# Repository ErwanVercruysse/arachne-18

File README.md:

<div align="center">

# ARACHNE / 18 — v4

**Six legs. Eighteen servos. Three monolithic moving links per leg.**

**18 × STS3215 12 V** · **3D printable** · **Onshape** · **MuJoCo + BAM**

[Onshape assembly](https://cad.onshape.com/documents/88edbeda4232642329938c14/w/19f5435855c2974f02fa7c68/e/916e6d95108202647e946643) · [Download print pack](print/ARACHNE_18_v4_print_pack.zip) · [Build guide](docs/build-guide.md) · [Simulation setup](docs/another-computer.md)

</div>

> **Deze fork (KVR-CIBER):** het ontwerp, de CAD en de simulatie hieronder zijn van [Tom Michiels](https://github.com/Tom-Michiels/arachne-18). Kobe heeft de robot echt gebouwd en er deze software voor geschreven, samen met [Claude Code](https://claude.com/claude-code).
>
> | Wat | Waar |
> |---|---|
> | Alle 18 servo's gekalibreerd, gewrichtslimieten gemeten | [`calibration/`](calibration/) |
> | Bewegingen op de echte robot: opstaan, lopen, draaien, dansen | [`tools/stand.py`](tools/stand.py), [`walk.py`](tools/walk.py), [`spin.py`](tools/spin.py), [`dance.py`](tools/dance.py), [`motion.py`](tools/motion.py) |
> | Besturen met een Bluetooth-gamepad, veilig via geplande gangen | [`tools/gamepad_robot.py`](tools/gamepad_robot.py), [`plan_gaits.py`](tools/plan_gaits.py) |
> | Live 3D-tweeling + camera + cockpit in de browser, met login | [`tools/live_twin.py`](tools/live_twin.py), [`tools/web/`](tools/web/), [`auth.py`](tools/auth.py) |
> | MuJoCo-simulatie in de browser | [`tools/sim_world.py`](tools/sim_world.py), [`tools/web/sim.html`](tools/web/sim.html) |
> | v4-robot van Tom Michiels samengevoegd (eendelige poten, 62 mm coxa, TPU-schoen): simulatie en beleid gebruiken de v4-maten | [`docs/revision-v4.md`](docs/revision-v4.md) |
> | Zelf lopen: het getrainde beleid live op de robot, met de IMU; houdt zich vlak op hellingen, tilt de poten hoger op oneffen grond | [`tools/policy_walk.py`](tools/policy_walk.py), [`terrain_gait.py`](tools/terrain_gait.py), [uitleg](docs/self-walking.md) |
> | Valbeveiliging: vrije val of omkantelen → zacht landen | [`tools/fall_guard.py`](tools/fall_guard.py), [`training/fall_test.py`](training/fall_test.py) |
> | Pakken: op vier poten iets van 12-15 cm breed oppakken met de voorpoten | [`tools/grab.py`](tools/grab.py), [`training/grab_test.py`](training/grab_test.py) |
> | BAM-metingen (38 / 173 / 263 / 383 g) en identificatie | [`bam_data/`](bam_data/), [`simulation/bam_identify.py`](simulation/bam_identify.py) |
> | ESP32-C3 one-wire firmware voor de STS3215-bus | [`firmware/`](firmware/) |
> | Android-app (wifi-scan, cockpit, "hey spin") | [arachne-app](https://github.com/KVR-CIBER/arachne-app) |

ARACHNE 18 is a compact six-legged prototype built around the owner's eighteen Feetech STS3215 12 V servos. This revision integrates the v4 leg and chassis into the complete robot: a single printed chassis, six identical leg modules, a removable controller carrier, and an organic ventilated canopy.

Each moving link is one printed piece. The tibia is symmetric, the horn cheeks have equal spacing, and the case cradles use the servo's factory mounting points. Local openings on the dummy side provide connector access. Horns sit inside the forks; recessed DIN 7380 button-head screws sit outside. There are no loose structural shims.

| Specification | v4 |
|---|---|
| Mechanism | Six yaw–hip–knee chains; 18 revolute joints |
| Chassis | 194 × 173.5 × 56 mm; six mounts on an 86 mm radius |
| Link geometry | Coxa 62 mm; hip offset −6.95 mm; femur 78 mm |
| Measured horn span | 36.5 mm; driven horn 2.5 mm, dummy horn 2.0 mm |
| Forks | 36.9 mm internal span; 5.5 mm cheeks; Ø7.3 mm center access |
| Battery envelope | 115 × 40 × 35 mm, excluding protruding plugs |
| Controller envelope | 90 × 60 × 18 mm; configurable 64 × 48 mm hole pattern |
| Printed parts | 8 unique files; 31 pieces including 6 TPU shoes and 4 PCB standoffs |
| Modelled hardware | 160 DIN 7380 M3 screws, 72 supplied PA2 case screws, 16 M3 inserts, 36 horns |
| Simulation | 19 rigid links, 18 actuators, 336 visual parts; estimated mass 2.333 kg |

## Inside the robot

| Removable electronics carrier | Symmetric six-leg layout |
|---|---|
|  |  |

The battery rests on the chassis and is retained by two straps. Four integrated posts support the controller carrier. Its mounting screws are reached through deep open wells. Two recessed M3 screws hold the canopy; straight tool openings make them accessible from above. Four small standoffs provide a 6 mm PCB air gap.

The front and rear pairs can touch their toes through a checked coordinated pose: inward yaw approximately 57.51°, hip −20°, knee 0°. This is a reach pose, not a walking command. Independent joint limits do not guarantee arbitrary combinations are collision-free.

## Print and assemble

Download the [STL bundle](print/ARACHNE_18_v4_print_pack.zip), [assembled STEP](cad/ARACHNE_18_assembly.step), or [individual STEP parts](cad/parts). STL units are millimetres; use 100% scale and the supplied orientations. All parts fit the H2D.

Start with one complete leg and a real servo. The [build guide](docs/build-guide.md) explains mounting order, screw lengths, insert positions, connector clearance and support removal. M3 plastic-thread joints use **Ruthex RX-M3x5.7**, with **Ø4.0 × 7 mm pilots**. Horn screws thread into metal horns; supplied case screws thread into the servo's factory mounting points.

The structural pieces have continuous flat bed faces. The curved canopy needs internal support; support is also needed locally beneath some fork bridges. All eight parts were sliced successfully with an A1 geometry proxy profile. **Reslice for your H2D**; no machine-ready G-code is supplied.

## Run MuJoCo

From a fresh clone, with Python 3.12:

```sh
git clone https://github.com/Tom-Michiels/arachne-18.git
cd arachne-18
python3.12 -m venv .venv
source .venv/bin/activate
python -m pip install -r simulation/requirements.txt
python simulation/simulate.py --headless --seconds 10 --voltage 11.1
python simulation/validate.py
```

For an interactive viewer on macOS:

```sh
mjpython simulation/grounded_demo.py --seconds 300
```

Use `python` for the viewer on Linux/Windows. On Windows activate with `.venv\Scripts\activate`. See [setup on another computer](docs/another-computer.md) and the [simulation guide](docs/simulation.md).

The animation is a BAM-driven body-height exercise. All six feet remain in contact; the base is free. The 12 V actuator parameters are an explicitly labelled approximation derived from BAM's identified 7.4 V model and manufacturer operating points. [BAM assumptions](docs/bam-model.md).

## Existing RL work

**No RL retraining was performed for v4.** Existing checkpoints, measurements and walking/jump/terrain videos are preserved. They were produced with earlier geometry and do not establish v4 performance. The training model and inverse kinematics now use v4 dimensions; controller and geometry compatibility tests are included.

### Browser simulation and cockpit (this fork)

`tools/live_twin.py` also serves a physics simulation at `/sim` (on the robot: `http://spin.local:5870/sim`). Everyone on the network sees and drives the same virtual robot: pick which parts to show (hidden parts also leave the physics mass), drive with the pad or WASD/QE in tripod, ripple or wave gait, tilt the body, run the shows, or run the real robot scripts (`stand.py`, `walk.py`, `spin.py`, `dance.py`) unchanged against virtual STS3215 servos. The meter panel shows supply current and voltage sag (5 A lab supply, 10 A, 3S LiPo, with brown-out), torque per servo, foot forces and the stability margin. The real servos are never touched.

```sh
.venv/bin/python tools/live_twin.py          # http://localhost:5870/sim
tools/deploy_pi.sh                           # copy to the Pi and restart the arachne-twin service
```

`/cockpit` puts the camera feed, the 3D view and the controls on one screen for a landscape tablet. It shows a picture-in-picture that you tap to swap. It has touch sticks, every move as a button, and gamepad support (Xbox/Recon or PlayStation, over USB or Bluetooth).

Cameras are found automatically:
- the Pi camera (`rpicam-vid`);
- USB webcams (`/dev/v4l/by-id/*usb*`, via ffmpeg);
- any MJPEG command in `ARACHNE_CAMERA`, `ARACHNE_CAMERA_1`, and so on.

Streams are served at `/camera.mjpg?cam=N`. A Pi 4 has a single CSI connector, so a second camera has to be USB.

An MPU6050 on I2C (SDA GPIO2, SCL GPIO3) is read by `tools/imu.py`. It appears in `/state` and in the cockpit. Its axes still have to be matched to the body by tilting the robot by hand.

The Android app (`~/arachne-app`, Capacitor) works like this:
- It scans the wifi for the twin.
- It opens the cockpit with an on-device voice assistant: say "hey spin, dans", "kom naar mij", "draai om" or "hoeveel volt?".
- Without a key it understands fixed Dutch commands. With a Claude API key it answers free questions and chooses moves through tool calls.
- Turning and walking distances are closed-loop on the measured pose.

[Training documentation](training/README.md) · [Archived locomotion videos](https://tom-michiels.github.io/arachne-18/) · [Revision notes](docs/revision-v4.md)

## Validation and limitations

Eight valid single-solid print parts and eight watertight single-component STLs pass the current checks. The release includes screw/print clearance checks, driver access checks, the isolated leg's factory-hole and connector tests, chassis installation tests, sampled dorsal motion and paired-toe reach evidence. MuJoCo passes topology, joint axes, standing at three voltages, reset reproducibility and grounded motion checks. [Scope and reports](docs/validation.md).

This is a digitally checked prototype. Real servo/horn/plug fit, print tolerances, insert pull-out strength, fatigue and payload capacity need a physical one-leg trial. The controller and battery are envelopes because exact models have not been specified. Servo visuals are simplified exterior references; the original vendor STEP is retained for mechanical checks.

## Files and sources

| Folder | Contents |
|---|---|
| [cad](cad) | Assembly, unique-part layout, individual STEP solids, dimensions and reference geometry |
| [print](print) | Oriented STLs, print quantities and downloadable print pack |
| [simulation](simulation) | MJCF, local-frame meshes, BAM parameters, runtime and validation |
| [src](src) | Parametric CadQuery source, exporters, CAD checks and Onshape mate tooling |
| [docs](docs) | English build, simulation, validation and development guides |
| [training](training) | Updated model adapter and preserved historical RL work |
| [tools](tools) | Real-robot tools: servo driver, calibration, live twin + browser simulation (`/sim`), motion scripts, Pi deploy |

Actuator modelling uses [Rhoban/BAM](https://github.com/Rhoban/bam); simulation uses [MuJoCo](https://github.com/google-deepmind/mujoco). See [third-party notices](THIRD_PARTY_NOTICES.md). No project-wide open-source license has been selected; bundled BAM material retains its Apache-2.0 license.

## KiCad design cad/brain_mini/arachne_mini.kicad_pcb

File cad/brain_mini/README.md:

# ARACHNE-18 mini brain board (v1.0)

Small 4-layer servo/IMU board for the hexapod that works **with the existing Raspberry Pi 4**: no CM5, no PI LINK.
The Pi talks to the ESP32-S3 over **one USB-C (board) <-> USB-A (Pi) cable** and gets its 5 V from the board.
It is the big board (`cad/brain_pcb`) without the CM5 part: same buck, 12 V entry, servo buses and IMU circuits.

| Block | Part | What it does |
|---|---|---|
| Real-time | **ESP32-S3-WROOM-1-N16R8** | drives both servo buses, reads the IMU, native USB to the Pi (`/dev/ttyACM0`) |
| IMU | **MPU-6050** (I2C on the ESP32, INT on IO6) | near the middle of the board |
| Sensors | G-V-S strip + 2x Qwiic | 19 free GPIOs, each with GND + 3.3 V, plus I2C |
| Servo buses | 2x (74AHCT1G126 + 74LVC1G34) | Feetech STS half-duplex, 5 V levels, 1 Mbaud |
| Legs | 6x Molex Mini-SPOX 5267-03A (22-03-5035, 2.50 mm, chamfered) | bus A = L1 L2 L3 (right), bus B = L4 L5 L6 (left) |
| Power | 2 big solder pads, P-MOSFET reverse protection, TVS, 2x 330 uF | 12 V straight to the servos |
| 5 V | TI **TPS54560B** buck, 5 V 5 A | Pi 4 (via the **5V PI** pads) + ESP32 + bus drivers |

Board: **92 x 70 mm**, 1.6 mm, 4 layers (F signals / In1 GND / In2 12 V / B signals + 5 V band to the Pi pads),
R6 corners, 4x M3 (3.2 mm) at (±41.5, ±25.5). Mounts on acrylic plate **v4**
(`cad/electronics_plate/make_electronics_plate_v4.py`): M3 x 12 -> PCB -> 8 mm spacer -> plate -> nut.

## Connections

* **USB-C "USB > PI 4"**: USB-C to USB-A cable to any Pi 4 USB port. Flash the ESP32 from the Pi
  (`arduino-cli` / `esptool` over `/dev/ttyACM0`) or from the Mac with the same cable. The Pi's 5 V on this cable
  only feeds the ESP32 side (through SS14 D7), so the ESP32 can be flashed without the 12 V battery.
* **5V PI pads** (top edge, next to the buck): 5 V / 3 A out for the Pi 4. Solder an 18-20 AWG pair to the Pi's
  GPIO pin 2 or 4 (+5 V) and pin 6 (GND), or to a cut USB-C lead plugged into the Pi power socket.
* **12V IN pads** (bottom-left): battery, 14-16 AWG; zip-tie slots on plate v4 as strain relief.
* **Servo (each leg):** `1 = GND, 2 = +12 V, 3 = DATA` (silkscreen G V S). Check against your cable first!

## ESP32-S3 pins

| GPIO | function | GPIO | function |
|---|---|---|---|
| 17 / 18 / 16 | bus A TX / RX / DE (UART1, DE = RTS) | 4 / 5 / 6 | IMU SDA / SCL / INT |
| 10 / 11 / 9 | bus B TX / RX / DE (UART2) | 1 | 12 V sense (100k/15k: V = adc x 7.67) |
| 19 / 20 | USB D- / D+ (to the Pi) | 2 | blue LED |
| 0 / EN | BOOT / RESET buttons | | |

**Sensor strip (bottom edge):** every free GPIO has its own **G - V - S** column (2.54 mm), like an Arduino sensor
shield, so a standard 3-wire sensor cable (GND, VCC, signal) plugs straight on.
* **V = 3.3 V.** The ESP32 pins are NOT 5 V tolerant: use 3.3 V sensors, or a level shifter for 5 V ones.
* Columns from left to right: IO7, IO15, IO8, IO3\*, IO46\*, IO12, IO13, IO14, IO21, IO47, IO48, IO45\*, IO38, IO39,
  IO40, IO41, IO42, TX43, RX44. The name is printed above every column.
* Next to the strip: **2x Qwiic / STEMMA QT** (JST-SH 4-pin, 3.3 V I2C, the same bus as the MPU-6050 on IO4/IO5).

\* strapping pins: don't pull them up/down at boot. IO35-37 are used by the octal PSRAM (N16R8).

**Servo connectors:** Molex Mini-SPOX **5267-03A** vertical headers (22-03-5035), the mating header for the **5264** plugs
(2.5 mm, with the chamfered corners) on the Feetech STS3215 / Waveshare cables. The chamfered side of the silkscreen
shows which way the plug goes in.

## Files

| File | |
|---|---|
| `arachne_mini.kicad_pro / .kicad_sch / .kicad_pcb` | open in KiCad 10 |
| `fab/` | gerbers zip, BOM + CPL with LCSC numbers for JLCPCB, schematic PDF, renders |
| `tools/design.py` | **single source of truth**: every part, net and position |
| `tools/build_all.sh` | regenerates everything (libraries, schematic, board, Freerouting + A* finisher, checks, fab) |

## Order (JLCPCB)

4 layers, 1.6 mm, upload `fab/arachne_mini_gerbers_JLCPCB.zip`, then BOM + CPL for assembly (LCSC numbers filled in).
The ESP32 antenna overhangs the top edge by ~6 mm on purpose.

## Before the first power-up

1. 12 V on the pads without Pi or servos: green LED, measure 5.0 V on the 5V PI pads and 3.3 V.
2. Connect the Pi (5V PI pads + USB cable), flash the ESP32.
3. Servos one leg at a time (torque on one servo at a time, 30 %).

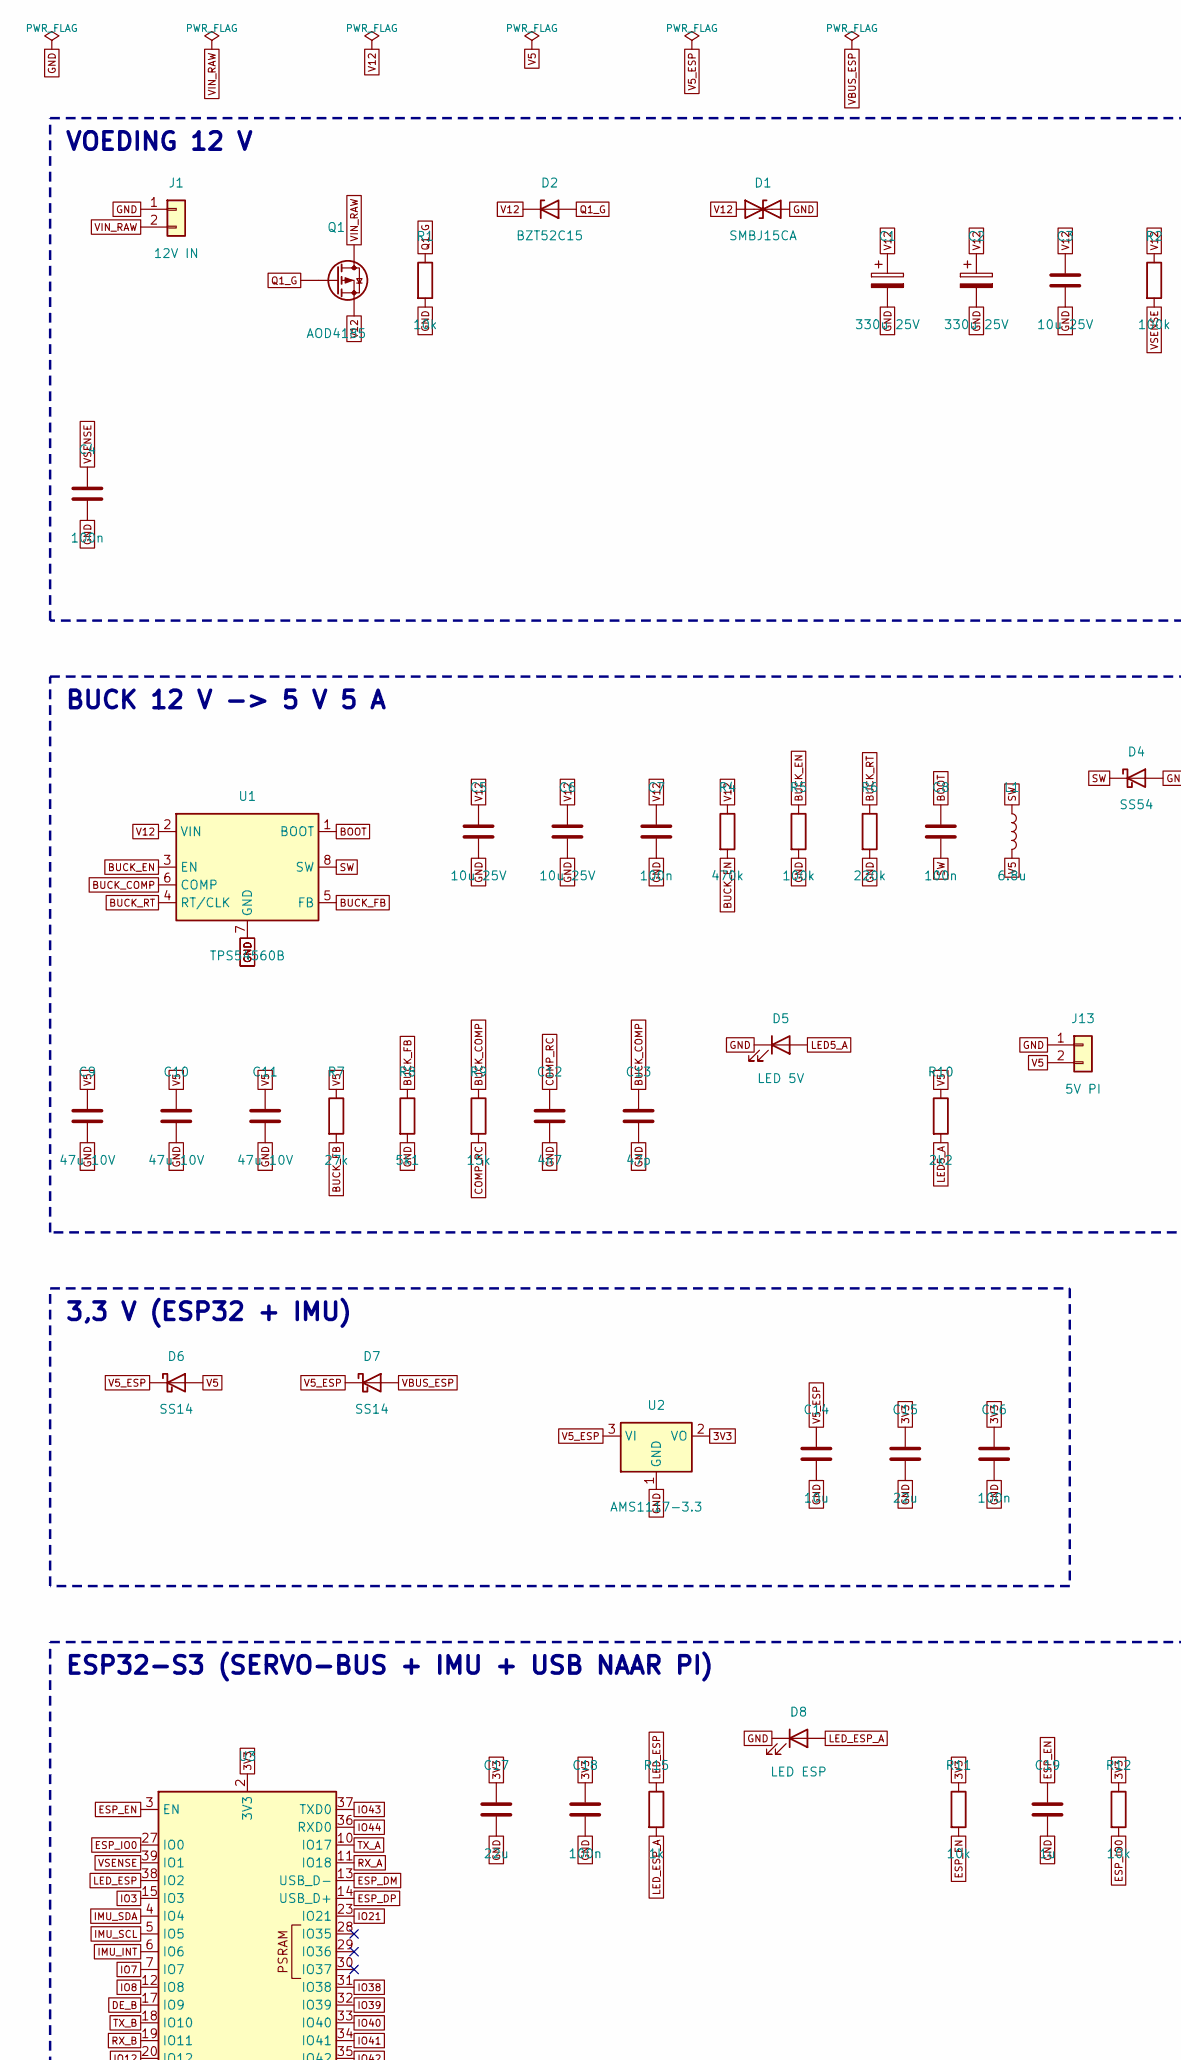
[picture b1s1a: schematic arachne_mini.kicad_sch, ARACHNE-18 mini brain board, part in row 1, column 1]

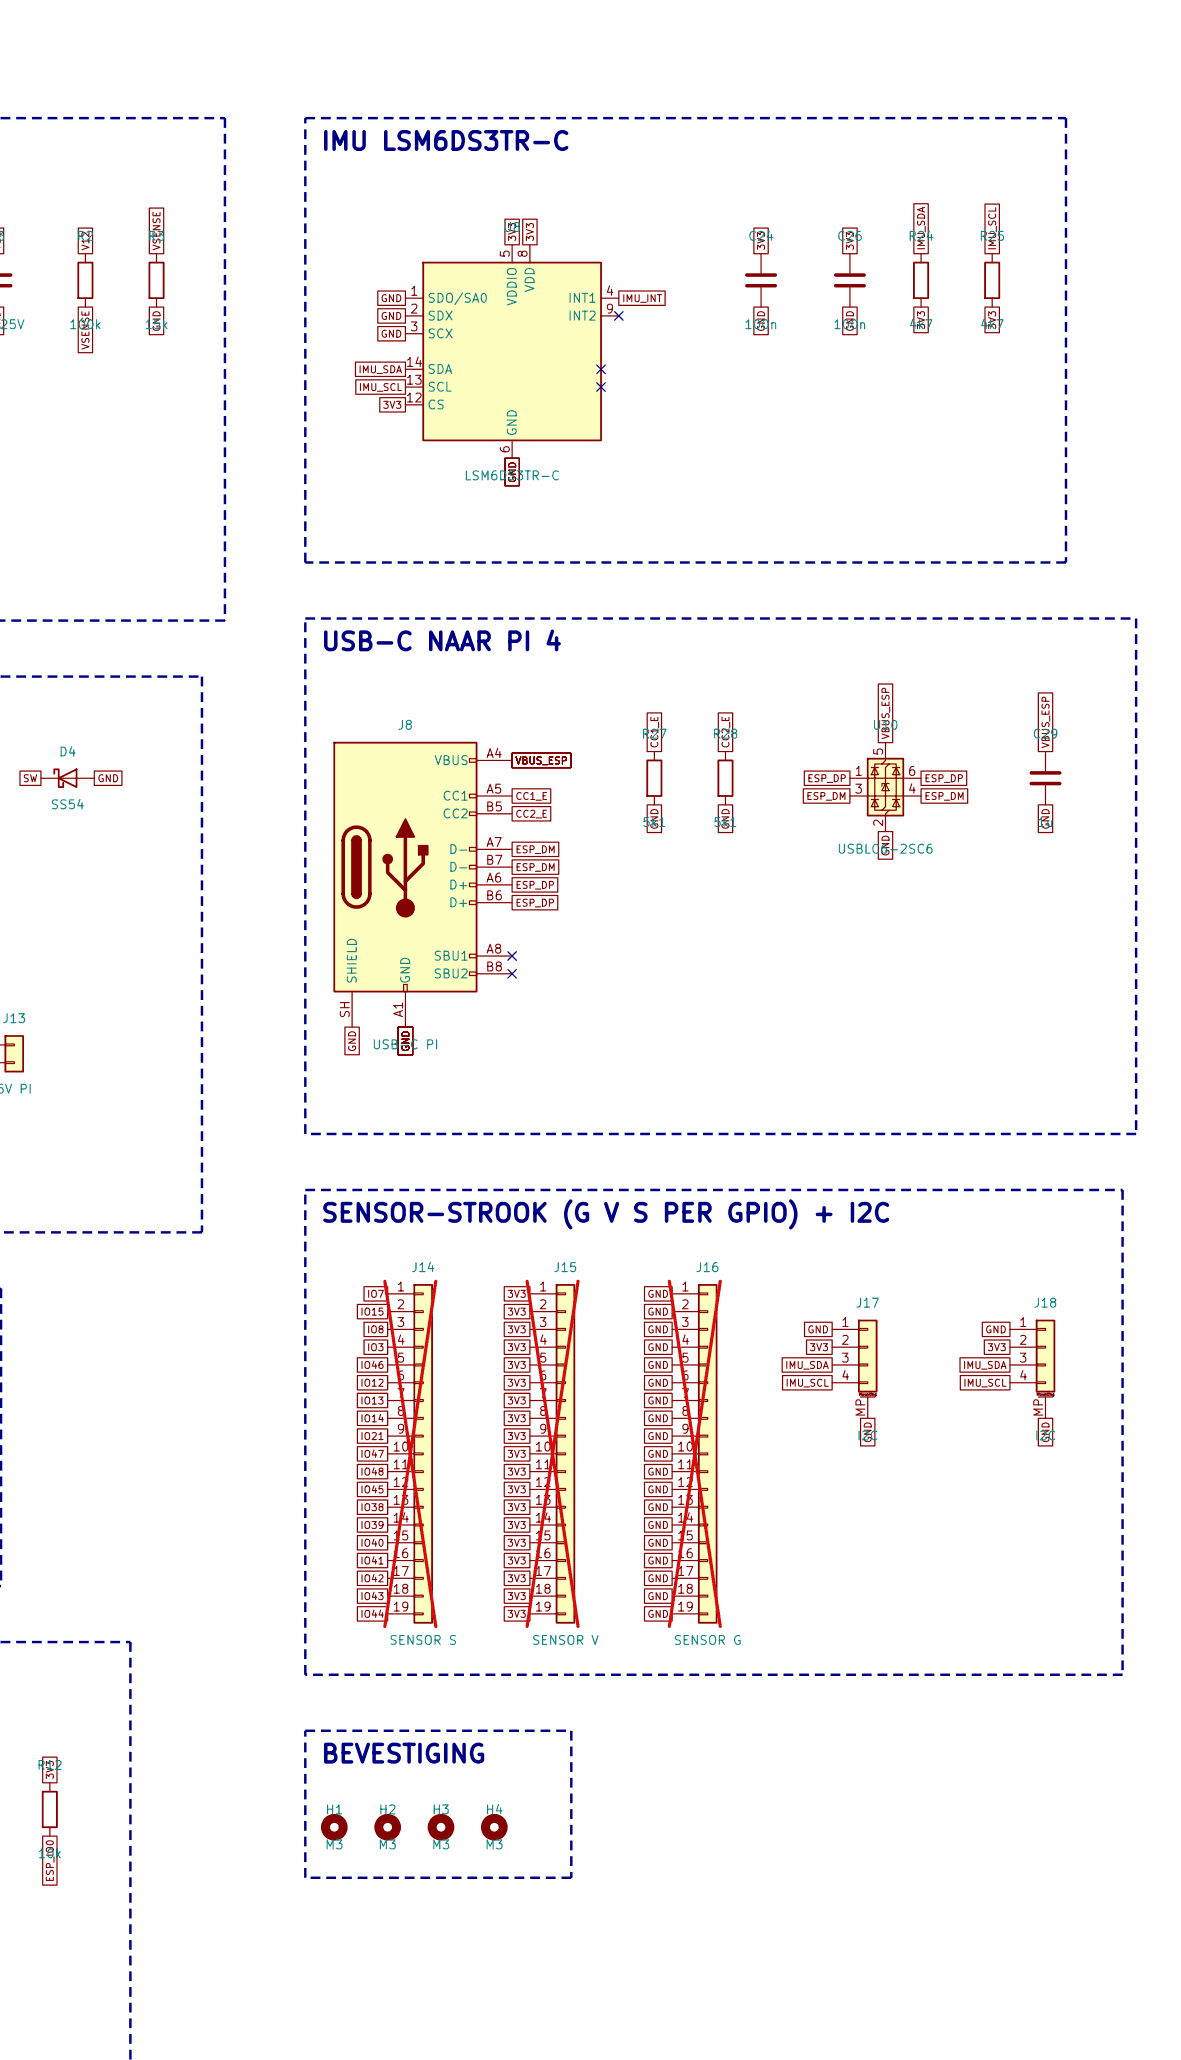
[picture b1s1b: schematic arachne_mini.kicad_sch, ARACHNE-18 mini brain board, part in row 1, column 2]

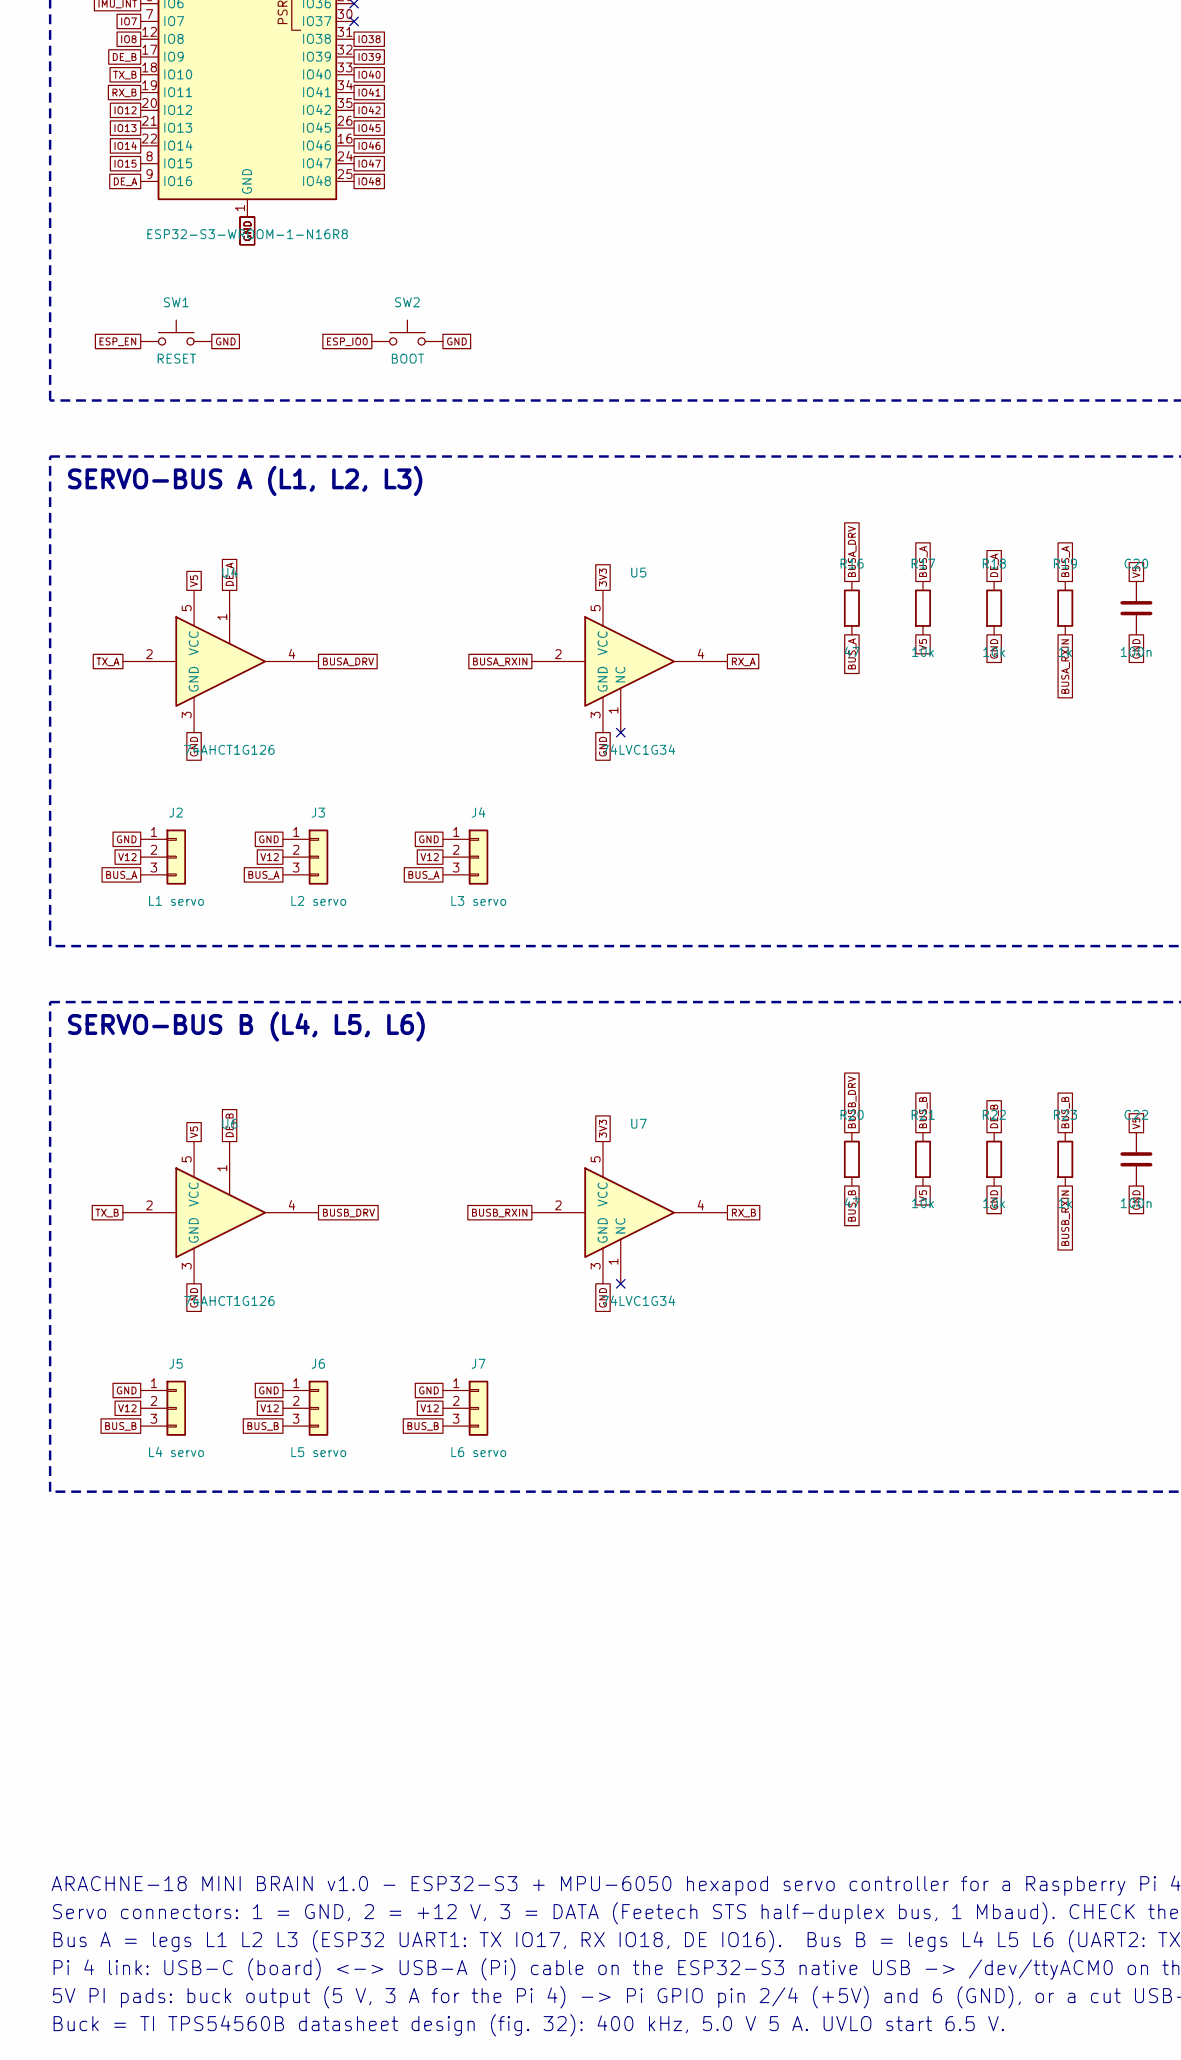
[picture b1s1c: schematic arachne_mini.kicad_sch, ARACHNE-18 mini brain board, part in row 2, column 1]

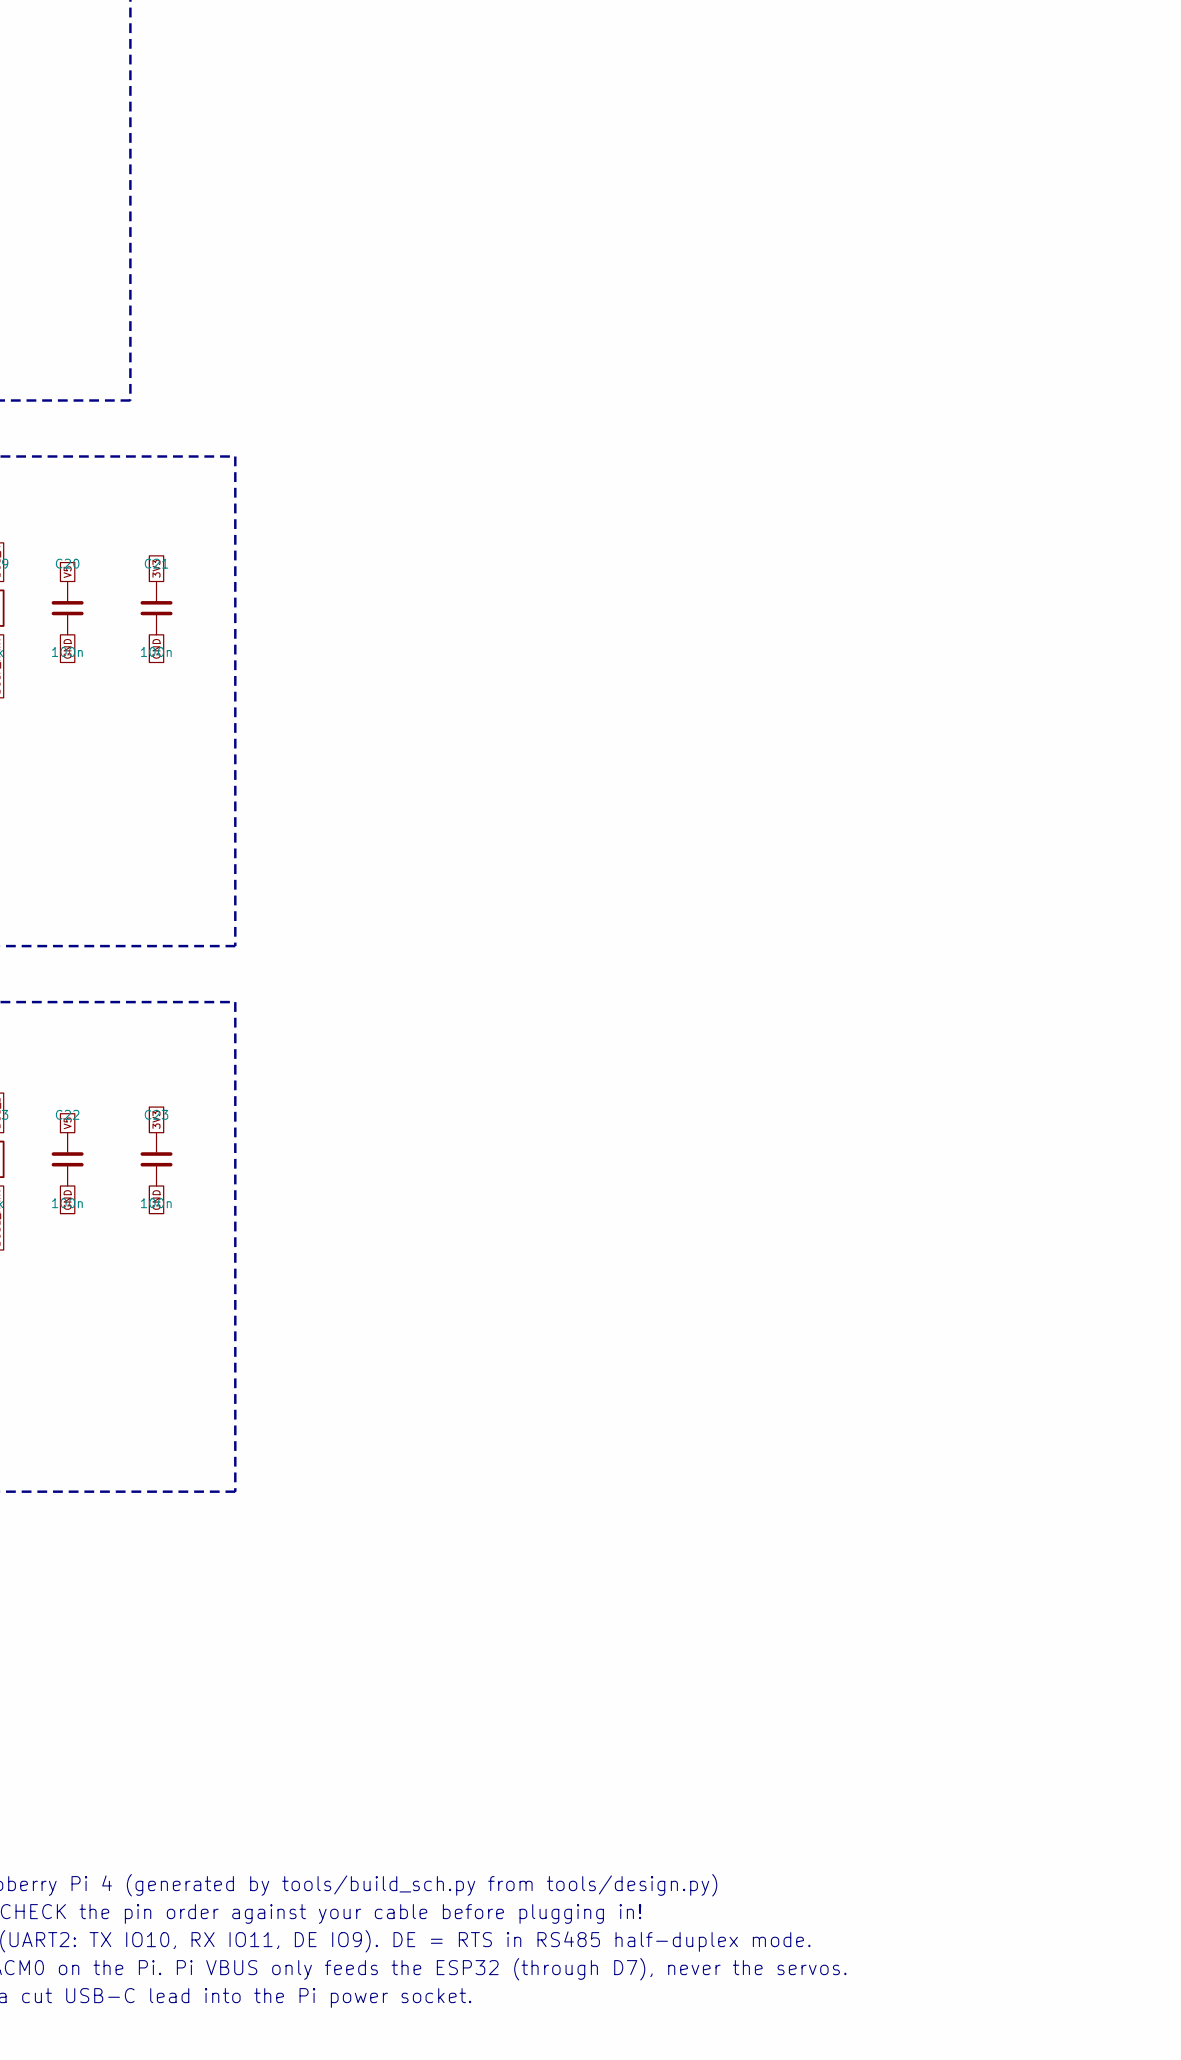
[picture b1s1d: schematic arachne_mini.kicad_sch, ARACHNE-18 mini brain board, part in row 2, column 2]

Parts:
C1, C2: 330u 25V; CP_Elec_8x10.5; MPN 330uF 25V 8x10.5 alu, STRONGLY recommen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
C3, C5, C6: 10u 25V; C_0805_2012Metric; MPN 0805 10u 25V X5R ceramic
C4, C7, C8, C16, C18, C20, C21, C22, C23, C24, C26: 100n; C_0603_1608Metric; MPN 0603 100n X7R ceramic
C9, C10, C11: 47u 10V; C_1206_3216Metric; MPN 1206 47u 10V X5R ceramic
C12: 4n7; C_0603_1608Metric; MPN 0603 4n7 X5R ceramic
C13: 47p; C_0603_1608Metric; MPN 0603 47p X7R ceramic
C14: 10u; C_0805_2012Metric; MPN 0805 10u X5R ceramic
C15, C17: 22u; C_0805_2012Metric; MPN 0805 22u X5R ceramic
C19, C29: 1u; C_0603_1608Metric; MPN 0603 1u X5R ceramic
D1: SMBJ15CA; D_SMB; MPN SMBJ15CA TVS (optional)
D2: BZT52C15; D_SOD-123; MPN BZT52C15 gate clamp (optional: AOD4185 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
D4: SS54; D_SMA; MPN SS54 (5 A 40 V Schottky, JLC basic)
D5: LED 5V; LED_0603_1608Metric; MPN LED 0603 red (JLC basic)
D6, D7: SS14; D_SMA; MPN SS14
D8: LED ESP; LED_0603_1608Metric; MPN LED 0603 red (JLC basic)
H1, H2, H3, H4: M3; MountingHole_3.2mm_M3
J1: 12V IN; SolderWire_2pad_P7mm_D2.2mm; MPN solder pads for 14-16 AWG
J2: L1 servo; Molex_5267-03A_1x03_P2.50mm_Vertical; MPN Molex 22-03-5035 / 5267-03A Mini-SPOX (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
J3: L2 servo; Molex_5267-03A_1x03_P2.50mm_Vertical; MPN Molex 22-03-5035 / 5267-03A Mini-SPOX (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
J4: L3 servo; Molex_5267-03A_1x03_P2.50mm_Vertical; MPN Molex 22-03-5035 / 5267-03A Mini-SPOX (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
J5: L4 servo; Molex_5267-03A_1x03_P2.50mm_Vertical; MPN Molex 22-03-5035 / 5267-03A Mini-SPOX (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
J6: L5 servo; Molex_5267-03A_1x03_P2.50mm_Vertical; MPN Molex 22-03-5035 / 5267-03A Mini-SPOX (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
J7: L6 servo; Molex_5267-03A_1x03_P2.50mm_Vertical; MPN Molex 22-03-5035 / 5267-03A Mini-SPOX (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
J8: USB-C PI; USB_C_Receptacle_HRO_TYPE-C-31-M-12; MPN HRO TYPE-C-31-M-12
J13: 5V PI; SolderWire_2pad_P5mm_D1.6mm_5V; MPN solder pads: 5 V 3 A to the Pi 4 (GPIO 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
J14: SENSOR S; PinHeader_1x19_P2.54mm_Vertical; MPN 1x19 pin header 2.54 mm (row S of the s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; not fitted
J15: SENSOR V; PinHeader_1x19_P2.54mm_Vertical; MPN 1x19 pin header 2.54 mm (row V of the s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; not fitted
J16: SENSOR G; PinHeader_1x19_P2.54mm_Vertical; MPN 1x19 pin header 2.54 mm (row G of the s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; not fitted
J17, J18: I2C; JST_SH_SM04B-SRSS-TB_1x04-1MP_P1.00mm_Horizontal; MPN JST SM04B-SRSS-TB (Qwiic / STEMMA QT, o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
L1: 6.8u; L_Bourns_SRP1038C_10.0x10.0mm; MPN Bourns SRP1038C-6R8M (6.8 uH, >= 8 A)
Q1: AOD4185; TO-252-2; MPN AOD4185 (P-MOSFET 40 V 40 A, reverse po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
R1, R11, R12, R17, R18, R21, R22: 10k; R_0603_1608Metric; MPN 0603 10k 1%
R2, R5: 100k; R_0603_1608Metric; MPN 0603 100k 1%
R3, R9: 15k; R_0603_1608Metric; MPN 0603 15k 1%
R4: 470k; R_0603_1608Metric; MPN 0603 470k 1%
R6: 220k; R_0603_1608Metric; MPN 0603 220k 1%
R7: 27k; R_0603_1608Metric; MPN 0603 27k 1%
R8, R27, R28: 5k1; R_0603_1608Metric; MPN 0603 5k1 1%
R10: 2k2; R_0603_1608Metric; MPN 0603 2k2 1%
R15, R19, R23: 1k; R_0603_1608Metric; MPN 0603 1k 1%
R16, R20: 47; R_0603_1608Metric; MPN 0603 47 1%
R24, R25: 4k7; R_0603_1608Metric; MPN 0603 4k7 1%
SW1: RESET; SW_Push_1P1T_NO_CK_KMR2; MPN CK KMR221G (4.2x2.8 tact); the S3 flash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
SW2: BOOT; SW_Push_1P1T_NO_CK_KMR2; MPN CK KMR221G (4.2x2.8 tact); the S3 flash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
U1: TPS54560B; Texas_R-PDSO-G8_EP2.95x4.9mm_Mask2.4x3.1mm_ThermalVias; MPN TPS54560BDDAR
U2: AMS1117-3.3; SOT-223-3_TabPin2; MPN AMS1117-3.3
U3: ESP32-S3-WROOM-1-N16R8; ESP32-S3-WROOM-1; MPN ESP32-S3-WROOM-1-N16R8
U4, U6: 74AHCT1G126; SOT-23-5; MPN 74AHCT1G126GW (TX driver, 5 V out)
U5, U7: 74LVC1G34; SOT-23-5; MPN 74LVC1G34GW (RX buffer, 5 V tolerant)
U8: LSM6DS3TR-C; LGA-14_3x2.5mm_P0.5mm_LayoutBorder3x4y; MPN LSM6DS3TR-C (6-axis IMU, I2C 0x6A)
U10: USBLC6-2SC6; SOT-23-6; MPN USBLC6-2SC6 ESD (optional)

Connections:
3V3: C15.1, C16.1, C17.1, C18.1, C21.1, C23.1, C24.1, C26.1, J15.1, J15.2, J15.3, J15.4, J15.5, J15.6, J15.7, J15.8, J15.9, J15.10, J15.11, J15.12, J15.13, J15.14, J15.15, J15.16, J15.17, J15.18, J15.19, J17.2, J18.2, R11.1, R12.1, R24.2, R25.2, U2.2 (VO), U3.2 (3V3), U5.5 (VCC), U7.5 (VCC), U8.5 (VDDIO), U8.8 (VDD), U8.12 (CS)
BOOT: C8.1, U1.1 (BOOT)
BUCK_COMP: C13.1, R9.1, U1.6 (COMP)
BUCK_EN: R4.2, R5.1, U1.3 (EN)
BUCK_FB: R7.2, R8.1, U1.5 (FB)
BUCK_RT: R6.1, U1.4 (RT/CLK)
BUSA_DRV: R16.1, U4.4
BUSA_RXIN: R19.2, U5.2
BUSB_DRV: R20.1, U6.4
BUSB_RXIN: R23.2, U7.2
BUS_A: J2.3, J3.3, J4.3, R16.2, R17.1, R19.1
BUS_B: J5.3, J6.3, J7.3, R20.2, R21.1, R23.1
CC1_E: J8.A5 (CC1), R27.1
CC2_E: J8.B5 (CC2), R28.1
COMP_RC: C12.1, R9.2
DE_A: R18.1, U3.9 (IO16), U4.1
DE_B: R22.1, U3.17 (IO9), U6.1
ESP_DM: J8.A7 (D-), J8.B7 (D-), U3.13 (USB_D-), U10.3 (I/O2), U10.4 (I/O2)
ESP_DP: J8.A6 (D+), J8.B6 (D+), U3.14 (USB_D+), U10.1 (I/O1), U10.6 (I/O1)
ESP_EN: C19.1, R11.2, SW1.1, U3.3 (EN)
ESP_IO0: R12.2, SW2.1, U3.27 (IO0)
GND: C1.2, C2.2, C3.2, C4.2, C5.2, C6.2, C7.2, C9.2, C10.2, C11.2, C12.2, C13.2, C14.2, C15.2, C16.2, C17.2, C18.2, C19.2, C20.2, C21.2, C22.2, C23.2, C24.2, C26.2, C29.2, D1.2 (A2), D4.2 (A), D5.1 (K), D8.1 (K), J1.1, J2.1, J3.1, J4.1, J5.1, J6.1, J7.1, J8.A1 (GND), J8.A12 (GND), J8.B1 (GND), J8.B12 (GND), J8.SH (SHIELD), J13.1, J16.1, J16.2, J16.3, J16.4, J16.5, J16.6, J16.7, J16.8, J16.9, J16.10, J16.11, J16.12, J16.13, J16.14, J16.15, J16.16, J16.17, J16.18, J16.19, J17.1, J17.MP (MountPin), J18.1, J18.MP (MountPin), R1.2, R3.2, R5.2, R6.2, R8.2, R18.2, R22.2, R27.2, R28.2, SW1.2, SW2.2, U1.7 (GND), U1.9 (GND), U2.1 (GND), U3.1 (GND), U3.40 (GND), U3.41 (GND), U4.3 (GND), U5.3 (GND), U6.3 (GND), U7.3 (GND), U8.1 (SDO/SA0), U8.2 (SDX), U8.3 (SCX), U8.6 (GND), U8.7 (GND), U10.2 (GND)
IMU_INT: U3.6 (IO6), U8.4 (INT1)
IMU_SCL: J17.4, J18.4, R25.1, U3.5 (IO5), U8.13 (SCL)
IMU_SDA: J17.3, J18.3, R24.1, U3.4 (IO4), U8.14 (SDA)
IO3: J14.4, U3.15 (IO3)
IO7: J14.1, U3.7 (IO7)
IO8: J14.3, U3.12 (IO8)
IO12: J14.6, U3.20 (IO12)
IO13: J14.7, U3.21 (IO13)
IO14: J14.8, U3.22 (IO14)
IO15: J14.2, U3.8 (IO15)
IO21: J14.9, U3.23 (IO21)
IO38: J14.13, U3.31 (IO38)
IO39: J14.14, U3.32 (IO39)
IO40: J14.15, U3.33 (IO40)
IO41: J14.16, U3.34 (IO41)
IO42: J14.17, U3.35 (IO42)
IO43: J14.18, U3.37 (TXD0)
IO44: J14.19, U3.36 (RXD0)
IO45: J14.12, U3.26 (IO45)
IO46: J14.5, U3.16 (IO46)
IO47: J14.10, U3.24 (IO47)
IO48: J14.11, U3.25 (IO48)
LED5_A: D5.2 (A), R10.2
LED_ESP: R15.1, U3.38 (IO2)
LED_ESP_A: D8.2 (A), R15.2
Q1_G: D2.2 (A), Q1.1 (G), R1.1
RX_A: U3.11 (IO18), U5.4
RX_B: U3.19 (IO11), U7.4
SW: C8.2, D4.1 (K), L1.1, U1.8 (SW)
TX_A: U3.10 (IO17), U4.2
TX_B: U3.18 (IO10), U6.2
V5: C9.1, C10.1, C11.1, C20.1, C22.1, D6.2 (A), J13.2, L1.2, R7.1, R10.1, R17.2, R21.2, U4.5 (VCC), U6.5 (VCC)
V5_ESP: C14.1, D6.1 (K), D7.1 (K), U2.3 (VI)
V12: C1.1, C2.1, C3.1, C5.1, C6.1, C7.1, D1.1 (A1), D2.1 (K), J2.2, J3.2, J4.2, J5.2, J6.2, J7.2, Q1.3 (S), R2.1, R4.1, U1.2 (VIN)
VBUS_ESP: C29.1, D7.2 (A), J8.A4 (VBUS), J8.A9 (VBUS), J8.B4 (VBUS), J8.B9 (VBUS), U10.5 (VBUS)
VIN_RAW: J1.2, Q1.2 (D)
VSENSE: C4.1, R2.2, R3.1, U3.39 (IO1)

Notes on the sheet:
VOEDING 12 V
BUCK 12 V -> 5 V 5 A
3,3 V (ESP32 + IMU)
ESP32-S3 (SERVO-BUS + IMU + USB NAAR PI)
SERVO-BUS A (L1, L2, L3)
SERVO-BUS B (L4, L5, L6)
IMU LSM6DS3TR-C
USB-C NAAR PI 4
SENSOR-STROOK (G V S PER GPIO) + I2C
BEVESTIGING
ARACHNE-18 MINI BRAIN v1.0 - ESP32-S3 + MPU-6050 hexapod servo controller for a Raspberry Pi 4 (generated by tools/build_sch.py from tools/design.py)
Servo connectors: 1 = GND, 2 = +12 V, 3 = DATA (Feetech STS half-duplex bus, 1 Mbaud). CHECK the pin order against your cable before plugging in!
Bus A = legs L1 L2 L3 (ESP32 UART1: TX IO17, RX IO18, DE IO16). Bus B = legs L4 L5 L6 (UART2: TX IO10, RX IO11, DE IO9). DE = RTS in RS485 half-duplex mode.
Pi 4 link: USB-C (board) <-> USB-A (Pi) cable on the ESP32-S3 native USB -> /dev/ttyACM0 on the Pi. Pi VBUS only feeds the ESP32 (through D7), never the servos.
5V PI pads: buck output (5 V, 3 A for the Pi 4) -> Pi GPIO pin 2/4 (+5V) and 6 (GND), or a cut USB-C lead into the Pi power socket.
Buck = TI TPS54560B datasheet design (fig. 32): 400 kHz, 5.0 V 5 A. UVLO start 6.5 V.

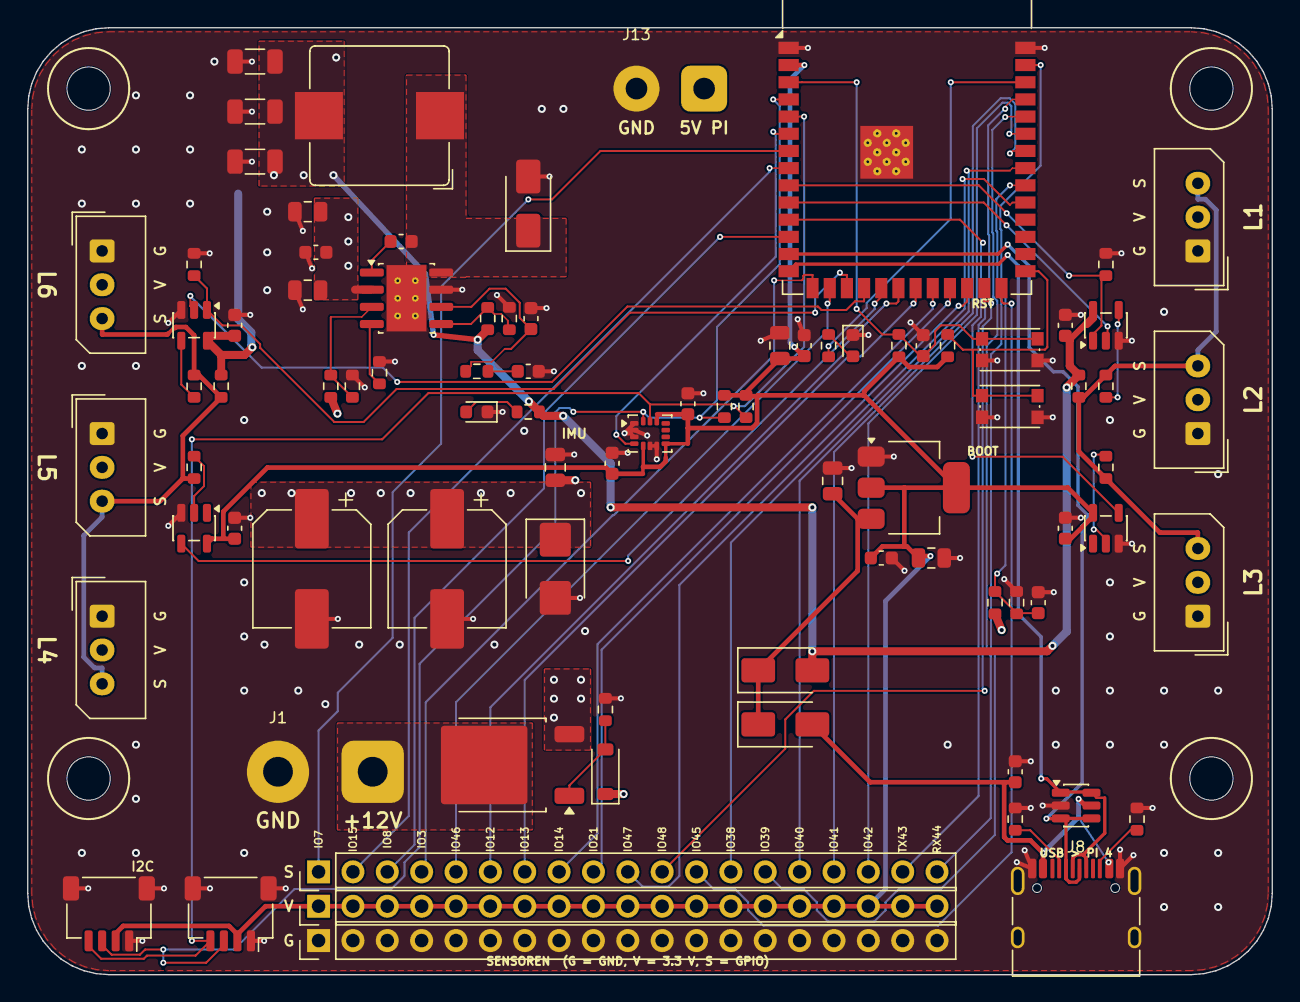
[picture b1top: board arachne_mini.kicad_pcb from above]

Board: 4 copper layers, 92.0 x 70.0 mm, 89 parts (0 on the bottom side), 59 nets.

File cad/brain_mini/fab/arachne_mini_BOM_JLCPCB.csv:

Comment,Designator,Footprint,Quantity,MPN / note,LCSC Part #
AOD4185,Q1,TO-252-2,1,"AOD4185 (P-MOSFET 40 V 40 A, reverse polarity)",C400894
10k,"R1,R11,R12,R17,R18,R21,R22",R_0603_1608Metric,7,0603 10k 1%,C25804
BZT52C15,D2,D_SOD-123,1,BZT52C15 gate clamp (optional: AOD4185 Vgs max 20 V),C173427
SMBJ15CA,D1,D_SMB,1,SMBJ15CA TVS (optional),C78410
330u 25V,"C1,C2",CP_Elec_8x10.5,2,"330uF 25V 8x10.5 alu, STRONGLY recommended for the servo current peaks",C350008
10u 25V / 10u,"C3,C5,C6,C14",C_0805_2012Metric,4,0805 10u 25V X5R ceramic,C15850
100k,"R2,R5",R_0603_1608Metric,2,0603 100k 1%,C25803
15k,"R3,R9",R_0603_1608Metric,2,0603 15k 1%,C22809
100n,"C4,C7,C8,C16,C18,C20,C21,C22,C23,C24,C26",C_0603_1608Metric,11,0603 100n X7R ceramic,C14663
TPS54560B,U1,Texas_R-PDSO-G8_EP2.95x4.9mm_Mask2.4x3.1mm_ThermalVias,1,TPS54560BDDAR,C1850354
470k,R4,R_0603_1608Metric,1,0603 470k 1%,C23178
220k,R6,R_0603_1608Metric,1,0603 220k 1%,C22961
6.8u,L1,L_Bourns_SRP1038C_10.0x10.0mm,1,"Bourns SRP1038C-6R8M (6.8 uH, >= 8 A)",C20804570
SS54,D4,D_SMA,1,"SS54 (5 A 40 V Schottky, JLC basic)",C22452
47u 10V,"C9,C10,C11",C_1206_3216Metric,3,1206 47u 10V X5R ceramic,C96123
27k,R7,R_0603_1608Metric,1,0603 27k 1%,C22967
5k1,"R8,R27,R28",R_0603_1608Metric,3,0603 5k1 1%,C23186
4n7,C12,C_0603_1608Metric,1,0603 4n7 X5R ceramic,C53987
47p,C13,C_0603_1608Metric,1,0603 47p X7R ceramic,C1671
LED 5V / LED ESP,"D5,D8",LED_0603_1608Metric,2,LED 0603 red (JLC basic),C2286
2k2,R10,R_0603_1608Metric,1,0603 2k2 1%,C4190
SS14,"D6,D7",D_SMA,2,SS14,C2480
AMS1117-3.3,U2,SOT-223-3_TabPin2,1,AMS1117-3.3,C6186
22u,"C15,C17",C_0805_2012Metric,2,0805 22u X5R ceramic,C45783
ESP32-S3-WROOM-1-N16R8,U3,ESP32-S3-WROOM-1,1,ESP32-S3-WROOM-1-N16R8,C2913202
1k,"R15,R19,R23",R_0603_1608Metric,3,0603 1k 1%,C21190
1u,"C19,C29",C_0603_1608Metric,2,0603 1u X5R ceramic,C15849
RESET / BOOT,"SW1,SW2",SW_Push_1P1T_NO_CK_KMR2,2,CK KMR221G (4.2x2.8 tact); the S3 flashes over native USB without it,C72443
74AHCT1G126,"U4,U6",SOT-23-5,2,"74AHCT1G126GW (TX driver, 5 V out)",C163712
74LVC1G34,"U5,U7",SOT-23-5,2,"74LVC1G34GW (RX buffer, 5 V tolerant)",C840096
47,"R16,R20",R_0603_1608Metric,2,0603 47 1%,C23182
L1 servo / L2 servo / L3 servo / L4 servo / L5 servo / L6 servo,"J2,J3,J4,J5,J6,J7",Molex_5267-03A_1x03_P2.50mm_Vertical,6,"Molex 22-03-5035 / 5267-03A Mini-SPOX (mates with the 5264 plug on Feetech cables), LCSC C45581067",C45581067
LSM6DS3TR-C,U8,LGA-14_3x2.5mm_P0.5mm_LayoutBorder3x4y,1,"LSM6DS3TR-C (6-axis IMU, I2C 0x6A)",C967633
4k7,"R24,R25",R_0603_1608Metric,2,0603 4k7 1%,C23162
USB-C PI,J8,USB_C_Receptacle_HRO_TYPE-C-31-M-12,1,HRO TYPE-C-31-M-12,C165948
USBLC6-2SC6,U10,SOT-23-6,1,USBLC6-2SC6 ESD (optional),C2687116
I2C,"J17,J18",JST_SH_SM04B-SRSS-TB_1x04-1MP_P1.00mm_Horizontal,2,"JST SM04B-SRSS-TB (Qwiic / STEMMA QT, optional)",C160404
